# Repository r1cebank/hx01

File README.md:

# MX01

A 8-bit CPU design

Recently I've been reading a lot about electroincs. I found building a 8-bit CPU from scratch will help me understand how modern CPU is designed.

__Note:__  I am a software developer by trade, but I always interested in electroincs. During college years, I have made multiple projects using Arduino, Netduino. I also coded a multi threaded os for Netduino. Building this 8 bit CPU is diffcult and I am basically follwing what's in the Digital Computer Electroincs by Malvino. If any of you reading this is electric engineer by trade and find anything to improve. Please let me know. Thank You

## Resources

[Building 8-bit computer](https://eater.net/8bit/) 

[Digital Computer Electronics](https://books.google.ca/books/about/Digital_Computer_Electronics.html?id=1QaMPwAACAAJ&redir_esc=y&hl=en)

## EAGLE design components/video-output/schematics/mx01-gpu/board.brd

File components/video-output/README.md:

# Video Output

The original design from Ben Eater does not have a solution to output video. But because we are building a "computer" we need a way to display output other than the 7 segment display. 

## High level design

We are following the retro design of video output. The entire system work as follows:

The video output system works separately from the entire system, it hooks up with the existing system (basically the display buffer is an extension of existing computer memory). The address range is undetermined. 

## How it works?

The framebuffer and display works on the separately Arduino board. Initially when the system is booted up, it will clear the framebuffer and create a loop that runs at 60hz dumping values from framebuffer to the display. It also sets an interrupt on the write line, so when the line goes from high to low (or low to high) it will modify the pixel value from that address.

## Parts

* Adafruit 1.44" TFT LCD [link](http://adafru.it/2088)
* Arduino Micro [link](https://store.arduino.cc/usa/arduino-micro)

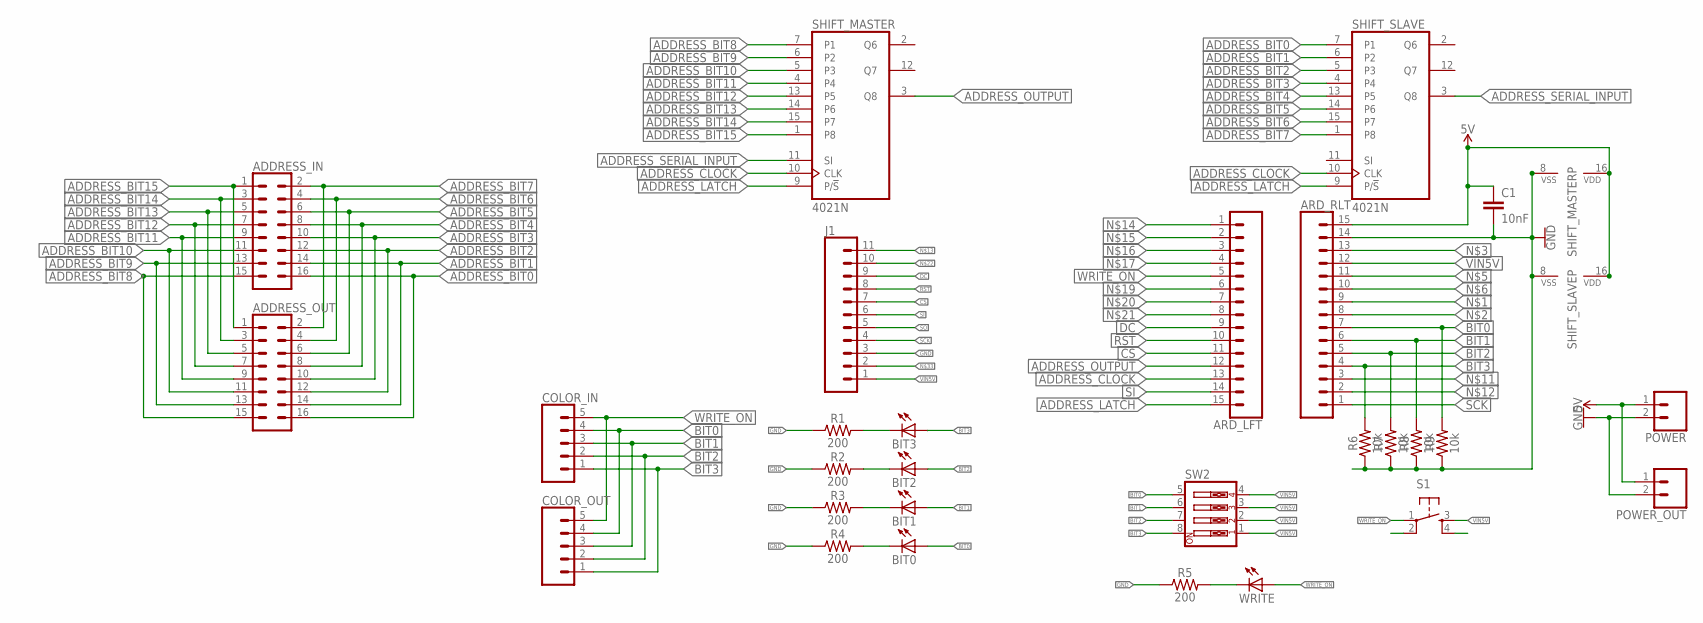
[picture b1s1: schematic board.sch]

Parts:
ADDRESS_IN: CONN_08X2; 2X8
ADDRESS_OUT: CONN_08X2; 2X8
ARD_LFT: CONN_15; 1X15
ARD_RLT: CONN_15; 1X15
BIT0, BIT1, BIT2, BIT3: LED5MM
C1: 10nF; CAP-PTH-10MM
COLOR_IN: CONN_05; 1X05
COLOR_OUT: CONN_05; 1X05
J1: CONN_11; 1X11
POWER: CONN_02; 1X02
POWER_OUT: CONN_02; 1X02
R1, R2, R3, R4, R5: 200; AXIAL-0.3
R6, R7, R8, R9: 10k; AXIAL-0.3
S1: TAC_SWITCHPTH; TACTILE-PTH
SHIFT_MASTER: 4021N; DIL16
SHIFT_SLAVE: 4021N; DIL16
SW2: SW_DIP-4; EDG-04
WRITE: LED5MM

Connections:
5V: ARD_RLT.15, C1.1, POWER.1, POWER_OUT.1, SHIFT_MASTER.16 (VDD), SHIFT_SLAVE.16 (VDD)
ADDRESS_BIT0: ADDRESS_IN.16, ADDRESS_OUT.16, SHIFT_SLAVE.7 (P1)
ADDRESS_BIT1: ADDRESS_IN.14, ADDRESS_OUT.14, SHIFT_SLAVE.6 (P2)
ADDRESS_BIT2: ADDRESS_IN.12, ADDRESS_OUT.12, SHIFT_SLAVE.5 (P3)
ADDRESS_BIT3: ADDRESS_IN.10, ADDRESS_OUT.10, SHIFT_SLAVE.4
ADDRESS_BIT4: ADDRESS_IN.8, ADDRESS_OUT.8, SHIFT_SLAVE.13 (P5)
ADDRESS_BIT5: ADDRESS_IN.6, ADDRESS_OUT.6, SHIFT_SLAVE.14 (P6)
ADDRESS_BIT6: ADDRESS_IN.4, ADDRESS_OUT.4, SHIFT_SLAVE.15 (P7)
ADDRESS_BIT7: ADDRESS_IN.2, ADDRESS_OUT.2, SHIFT_SLAVE.1 (P8)
ADDRESS_BIT8: ADDRESS_IN.15, ADDRESS_OUT.15, SHIFT_MASTER.7 (P1)
ADDRESS_BIT9: ADDRESS_IN.13, ADDRESS_OUT.13, SHIFT_MASTER.6 (P2)
ADDRESS_BIT10: ADDRESS_IN.11, ADDRESS_OUT.11, SHIFT_MASTER.5 (P3)
ADDRESS_BIT11: ADDRESS_IN.9, ADDRESS_OUT.9, SHIFT_MASTER.4
ADDRESS_BIT12: ADDRESS_IN.7, ADDRESS_OUT.7, SHIFT_MASTER.13 (P5)
ADDRESS_BIT13: ADDRESS_IN.5, ADDRESS_OUT.5, SHIFT_MASTER.14 (P6)
ADDRESS_BIT14: ADDRESS_IN.3, ADDRESS_OUT.3, SHIFT_MASTER.15 (P7)
ADDRESS_BIT15: ADDRESS_IN.1, ADDRESS_OUT.1, SHIFT_MASTER.1 (P8)
ADDRESS_CLOCK: ARD_LFT.13, SHIFT_MASTER.10 (CLK), SHIFT_SLAVE.10 (CLK)
ADDRESS_LATCH: ARD_LFT.15, SHIFT_MASTER.9 (P/!S), SHIFT_SLAVE.9 (P/!S)
ADDRESS_OUTPUT: ARD_LFT.12, SHIFT_MASTER.3 (Q8)
ADDRESS_SERIAL_INPUT: SHIFT_MASTER.11 (SI), SHIFT_SLAVE.3 (Q8)
BIT0: ARD_RLT.7, BIT0.A, COLOR_IN.4, COLOR_OUT.4, R9.P$2 (2), SW2.5
BIT1: ARD_RLT.6, BIT1.A, COLOR_IN.3, COLOR_OUT.3, R8.P$2 (2), SW2.6
BIT2: ARD_RLT.5, BIT2.A, COLOR_IN.2, COLOR_OUT.2, R7.P$2 (2), SW2.7
BIT3: ARD_RLT.4, BIT3.A, COLOR_IN.1, COLOR_OUT.1, R6.P$2 (2), SW2.8
CS: ARD_LFT.11, J1.7
DC: ARD_LFT.9, J1.9
GND: ARD_RLT.14, C1.2, J1.3, POWER.2, POWER_OUT.2, R1.P$1 (1), R2.P$1 (1), R3.P$1 (1), R4.P$1 (1), R5.P$1 (1), R6.P$1 (1), R7.P$1 (1), R8.P$1 (1), R9.P$1 (1), SHIFT_MASTER.8 (VSS), SHIFT_SLAVE.8 (VSS)
unnamed: R5.P$2 (2), WRITE.K (C)
unnamed: BIT0.K (C), R4.P$2 (2)
unnamed: BIT1.K (C), R3.P$2 (2)
unnamed: BIT2.K (C), R2.P$2 (2)
unnamed: BIT3.K (C), R1.P$2 (2)
RST: ARD_LFT.10, J1.8
SCK: ARD_RLT.1, J1.4
SI: ARD_LFT.14, J1.6
SO: J1.5
VIN5V: ARD_RLT.12, J1.1, S1.3, SW2.1, SW2.2, SW2.3, SW2.4
WRITE_ON: ARD_LFT.5, COLOR_IN.5, COLOR_OUT.5, S1.1, WRITE.A

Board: 2 copper layers, 28 parts (0 on the bottom side), 38 nets, no tracks yet.

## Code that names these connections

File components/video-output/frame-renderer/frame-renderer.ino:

#include <Adafruit_GFX.h>    // Core graphics library
#include <Adafruit_ST7735.h> // Hardware-specific library
#include <SPI.h>

// Pin configs
#define TFT_CS     8
#define TFT_RST    7
#define TFT_DC     6
#define INPUT_DATA 9
#define INPUT_CLOCK 10
#define INPUT_LATCH 12

const byte interruptPin = 2;
const byte color1bit = A3;
const byte color2bit = A2;
const byte color3bit = A1;
const byte color4bit = A0;

Adafruit_ST7735 tft = Adafruit_ST7735(TFT_CS,  TFT_DC, TFT_RST);

volatile byte frameBuffer[32][32];
volatile byte addressValue = 0;

const uint16_t colorMap[] = {
    0x0000,
    0x8000,
    0xF800,
    0xF81F,
    0x0410,
    0x0400,
    0x07E0,
    0x07FF,
    0x0010,
    0x8010,
    0x001F,
    0xC618,
    0x8410,
    0x8400,
    0xFFE0,
    0xFFFF
};

void setup() {
    // Init input
    pinMode(INPUT_DATA, INPUT);
    pinMode(INPUT_LATCH, OUTPUT);
    pinMode(INPUT_CLOCK, OUTPUT); 
    // Init serial
    Serial.begin(9600);
    Serial.println("Hello! mx01 gpu");
    // Init display
    tft.initR(INITR_144GREENTAB);
    tft.fillScreen(ST7735_YELLOW);
    // Fille framebuffer with black
    for (int i = 0; i < 32; i++) {
        for (int j = 0; j < 32; j++) {
            frameBuffer[i][j] = B00000000;
        }
    }
    // Attach write interrupt
    attachInterrupt(digitalPinToInterrupt(interruptPin), updateFramebuffer, FALLING);
}

void loop() {
    // put your main code here, to run repeatedly:
    renderBuffer();
}

byte boolArrayToByte(boolean* bits){
    int ret = 0;
    int tmp;
    for (int i = 0; i < 4; i++) {
        tmp = bits[i];
        ret |= tmp << (4 - i - 1);
    }
    return ret;
}

uint8_t fixedShiftIn(uint8_t dataPin, uint8_t clockPin, uint8_t bitOrder) {
	uint8_t value = 0;
	uint8_t i;

	for (i = 0; i < 8; ++i) {
		digitalWrite(clockPin, LOW);
		if (bitOrder == LSBFIRST)
			value |= digitalRead(dataPin) << i;
		else
			value |= digitalRead(dataPin) << (7 - i);
		digitalWrite(clockPin, HIGH);
	}
	return value;
}

void updateFramebuffer() {
    // read from register
    digitalWrite(INPUT_LATCH, 1);
    delayMicroseconds(20);

    //Set latch pin to 0 to get data from the CD4021
    digitalWrite(INPUT_LATCH, 0);

    //Get CD4021 register data in byte variable
    addressValue = fixedShiftIn(INPUT_DATA, INPUT_CLOCK, MSBFIRST);
    Serial.print(addressValue);
    Serial.print("-");
    Serial.println(addressValue, BIN);
    const boolean bit1 = digitalRead(color1bit);
    const boolean bit2 = digitalRead(color2bit);
    const boolean bit3 = digitalRead(color3bit);
    const boolean bit4 = digitalRead(color4bit);
    const boolean bits[] = {bit4, bit3, bit2, bit1};
    frameBuffer[1][1] = boolArrayToByte(bits); // Fixed address while I wait for shift register to arrive
}

void renderBuffer() {
    for (int y = 0; y < 32; y++) {
        for (int x = 0; x < 32; x++) {
            tft.fillRect(x * 4, y * 4 , 4, 4, colorMap[frameBuffer[x][y]]);
            // tft.drawRect(tft.width()/2 -x/2, tft.height()/2 -x/2 , x, x, color2);
        }
    }
}

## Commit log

2018-01-08 Adding more stuff
2018-01-10 Adding video output
2018-01-12 Adding microcode
2018-01-13 Day 1
2018-01-14 day 2 gpu
2018-01-20 adding schematics
2018-01-27 adding shift registers
2018-02-03 Finish board v.0.01

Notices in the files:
parts and their libraries:
SparkFun-Connectors: Licensing: Creative Commons ShareAlike 4.0 International - https://creativecommons.org/licenses/by-sa/4.0
